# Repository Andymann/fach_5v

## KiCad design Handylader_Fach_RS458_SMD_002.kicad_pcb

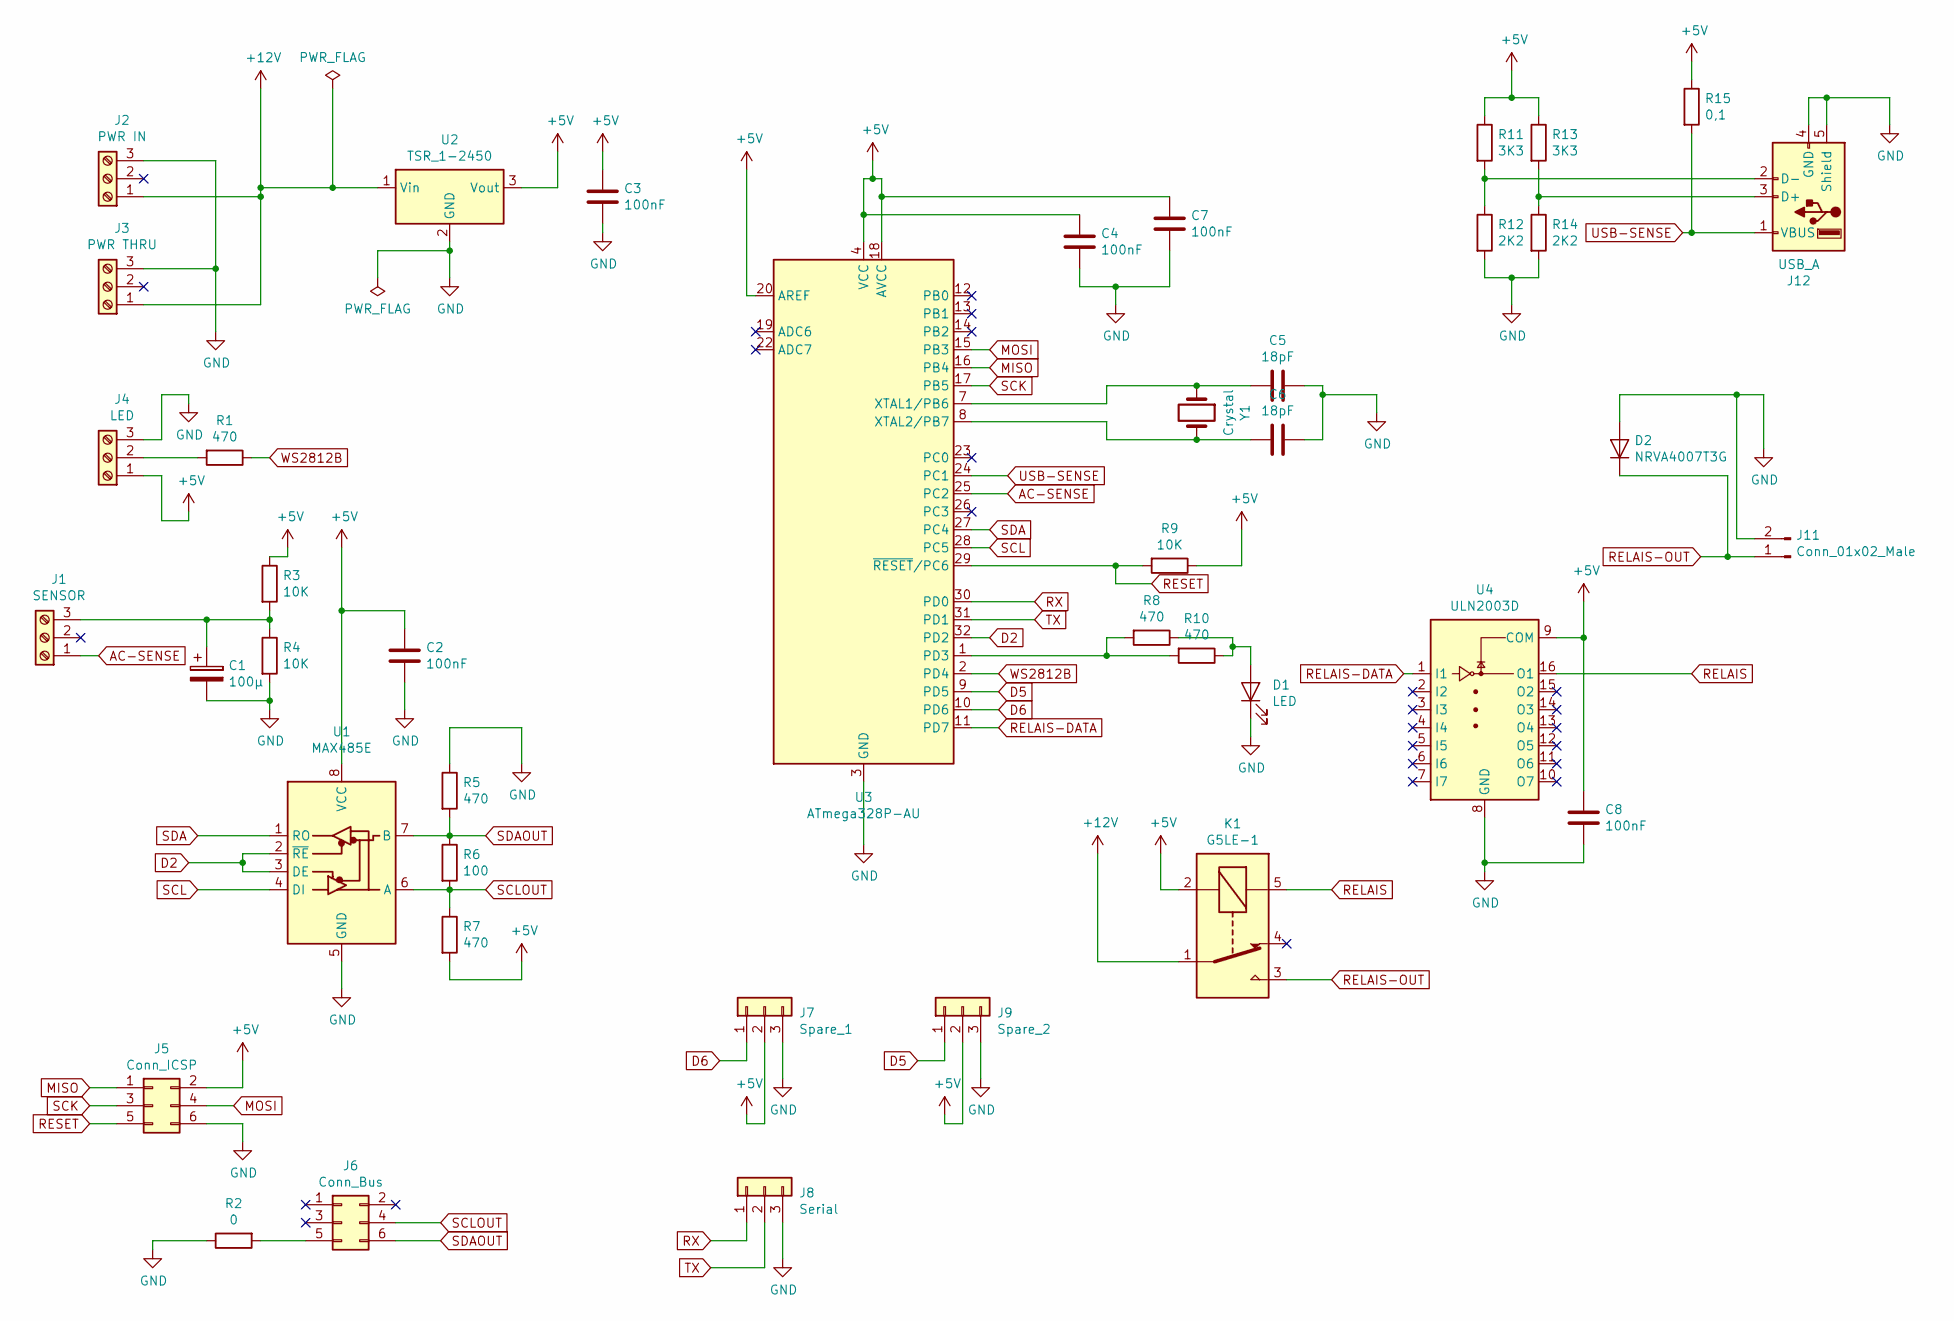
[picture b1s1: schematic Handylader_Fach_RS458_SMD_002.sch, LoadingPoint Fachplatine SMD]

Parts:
C1: 100µ; C_0603_1608Metric
C2, C3, C4, C7, C8: 100nF; C_0603_1608Metric
C5, C6: 18pF; C_0603_1608Metric
D1: LED; LED_0603_1608Metric
D2: NRVA4007T3G; D_SMA
J1: SENSOR; TerminalBlock_TE_282834-3_1x03_P2.54mm_Horizontal
J2: PWR IN; TerminalBlock_TE_282834-3_1x03_P2.54mm_Horizontal
J3: PWR THRU; TerminalBlock_TE_282834-3_1x03_P2.54mm_Horizontal
J4: LED; TerminalBlock_TE_282834-3_1x03_P2.54mm_Horizontal
J5: Conn_ICSP; PinHeader_2x03_P2.54mm_Vertical_SMD
J6: Conn_Bus; PinHeader_2x03_P2.54mm_Vertical_SMD
J7: Spare_1; PinHeader_1x03_P2.54mm_Vertical
J8: Serial; PinHeader_1x03_P2.54mm_Vertical
J9: Spare_2; PinHeader_1x03_P2.54mm_Vertical
J11: Conn_01x02_Male; PinHeader_1x02_P2.54mm_Vertical
J12: USB_A; Wurth_USB_A_62900416021
K1: G5LE-1; Relay_SPDT_Omron-G5LE-1
R1, R5, R7, R8, R10: 470; R_0603_1608Metric
R2: 0; R_0603_1608Metric
R3, R4, R9: 10K; R_0603_1608Metric
R6: 100; R_0603_1608Metric
R11, R13: 3K3; R_0603_1608Metric
R12, R14: 2K2; R_0603_1608Metric
R15: 0,1; R_0603_1608Metric
U1: MAX485E; SOIC-8_3.9x4.9mm_P1.27mm
U2: TSR_1-2450; Converter_DCDC_TRACO_TSR-1_THT
U3: ATmega328P-AU; TQFP-32_7x7mm_P0.8mm
U4: ULN2003D; SOIC-16_3.9x9.9mm_P1.27mm
Y1: Crystal; Crystal_SMD_HC49-SD

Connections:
+5V: C2.1, C3.1, C4.1, C7.1, C8.1, J4.1, J5.2, J7.2, J9.2, K1.2, R3.1, R7.2, R9.1, R11.1, R13.1, R15.1, U1.8 (VCC), U2.3 (Vout), U3.4 (VCC), U3.6 (VCC), U3.18 (AVCC), U3.20 (AREF), U4.9 (COM)
+12V: J2.1, J3.1, K1.1, U2.1 (Vin)
AC-SENSE: J1.1, U3.25 (PC2)
D2: U1.2 (~RE), U1.3 (DE), U3.32 (PD2)
D5: J9.1, U3.9 (PD5)
D6: J7.1, U3.10 (PD6)
GND: C1.2, C2.2, C3.2, C4.2, C5.1, C6.1, C7.2, C8.2, D1.1 (K), D2.2 (A), J2.3, J3.3, J4.3, J5.6, J7.3, J8.3, J9.3, J11.2, J12.4 (GND), J12.5 (Shield), R2.1, R4.2, R5.1, R12.2, R14.2, U1.5 (GND), U2.2 (GND), U3.3 (GND), U3.5 (GND), U3.21 (GND), U4.8 (GND)
MISO: J5.1, U3.16 (PB4)
MOSI: J5.4, U3.15 (PB3)
unnamed: C1.1, J1.3, R3.2, R4.1
unnamed: C5.2, U3.7 (XTAL1/PB6), Y1.1
unnamed: C6.2, U3.8 (XTAL2/PB7), Y1.2
unnamed: D1.2 (A), R8.1, R10.1
unnamed: J4.2, R1.2
unnamed: J6.5, R2.2
unnamed: J12.2 (D-), R11.2, R12.1
unnamed: J12.3 (D+), R13.2, R14.1
unnamed: R8.2, R10.2, U3.1 (PD3)
RELAIS: K1.5, U4.16 (O1)
RELAIS-DATA: U3.11 (PD7), U4.1 (I1)
RELAIS-OUT: D2.1 (K), J11.1, K1.3
RESET: J5.5, R9.2, U3.29 (~RESET~/PC6)
RX: J8.1, U3.30 (PD0)
SCK: J5.3, U3.17 (PB5)
SCL: U1.4 (DI), U3.28 (PC5)
SCLOUT: J6.4, R6.2, R7.1, U1.6 (A)
SDA: U1.1 (RO), U3.27 (PC4)
SDAOUT: J6.6, R5.2, R6.1, U1.7 (B)
TX: J8.2, U3.31 (PD1)
USB-SENSE: J12.1 (VBUS), R15.2, U3.24 (PC1)
WS2812B: R1.1, U3.2 (PD4)

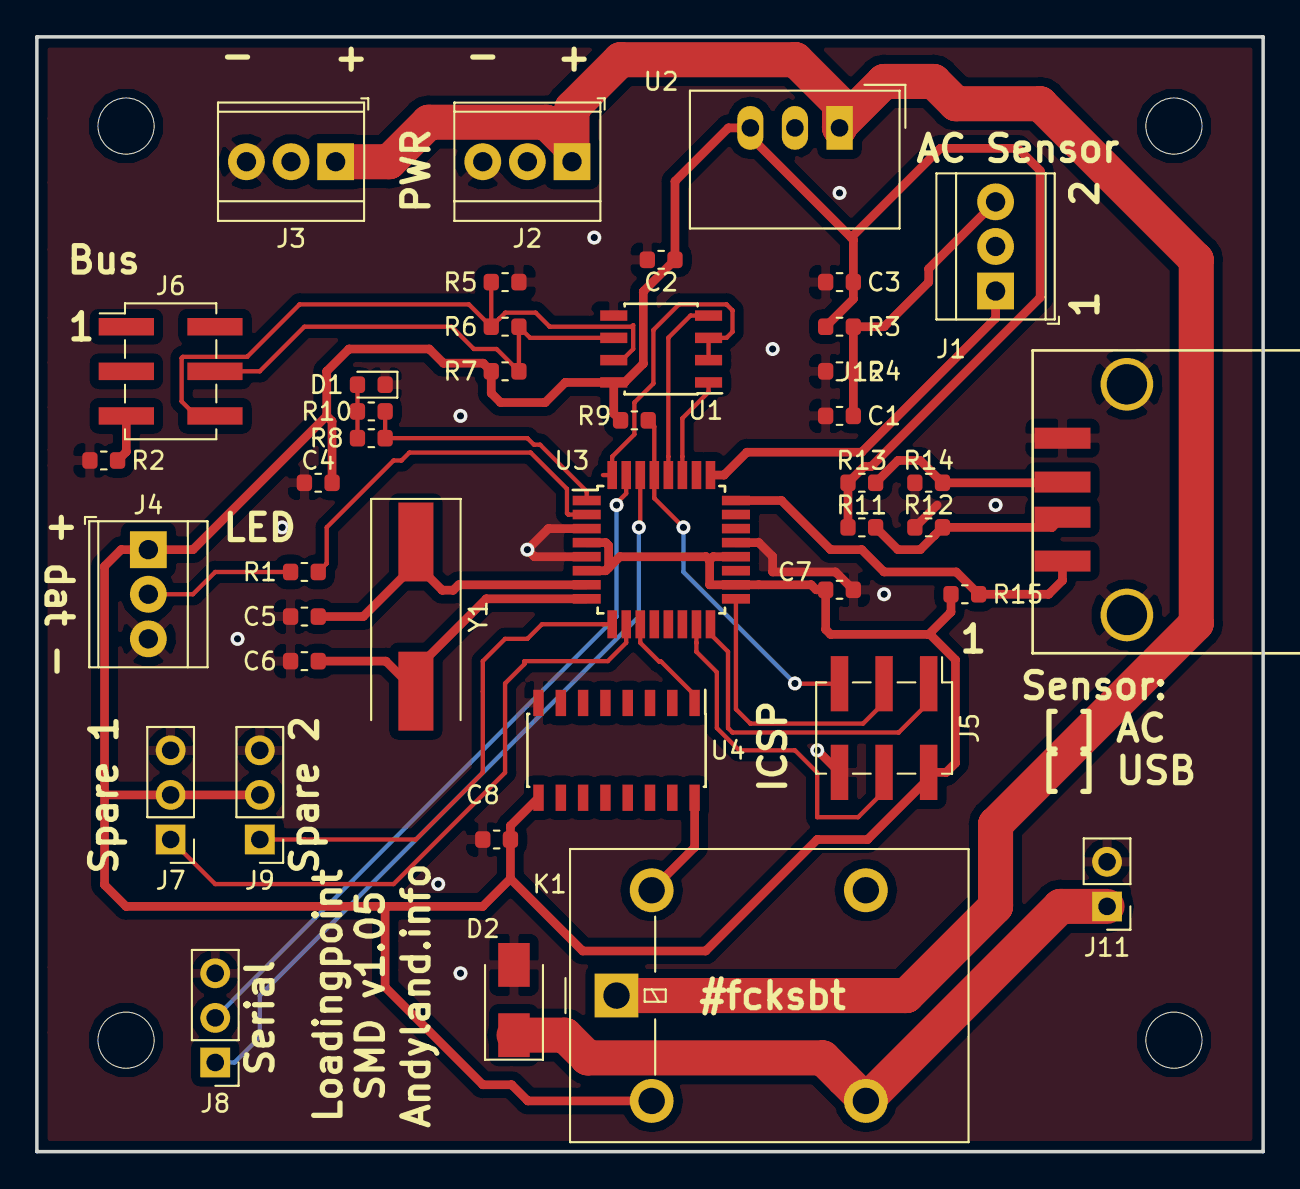
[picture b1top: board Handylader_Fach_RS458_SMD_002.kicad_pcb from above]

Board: 2 copper layers, 69.8 x 63.5 mm, 42 parts (0 on the bottom side), 31 nets.
